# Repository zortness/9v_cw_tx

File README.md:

# 9V QRP Micro Transciever

Based on the schematic and work of Jeff Anderson, [K6JCA](https://www.qrz.com/db/k6jca)
and [this blog post](http://k6jca.blogspot.com/2009/08/9v-qrp-transceiver.html).

Thank you to Jeff for your help in debugging my implementation of your design.

## About

This is a very simple, direct conversion CW transciever that will operate on the 40m 
amateur radio band. It requires an external speaker or headphones, an external antenna,
and an external keyer for sending. 

This design is intended to allow modifying the center frequency of the transciever by
changing out the oscillator crystal without re-soldering any parts. 

**This is still a work in progress.**

I have devided up the functionality across two small PCBs and used a 8-pin jumper between them.
This gives a bit more room to spread out the components, and hopefully avoid unwanted interactions.
It should also give a bit larger ground plane, which should help with environmental sensitivity.

The transmitter has an observed harmonic transmission on 14m, which might necessitate an external 
band pass filter board at some point.

The power output in my experiements so far has been quite small, in the 50-100mW range. 

The effective receive and transmit frequencies can also be apart from one another by enough that
you may not hear someone responding directly on your transmit frequency. This seems to be worse
at either extreme of the VXO adjustment, but not verified by data yet.

## Schematics

## Board Layouts

## ProtoBoard Prototype 

This prototype is extremely sensitive to capacitance (even touch), and lacks a true ground plane,
though I added through-hole-pins to act as grounding feet on my steel work table. 

## SMD Prototypes

I've gone through a few SMD prototypes and made a number of pad and routing mistakes. I also chose
a number of parts poorly or just completely misread the units on the part values (nH != uH, pF != uF). 

I will update when one of the boards can operate without any further modification.

## SMD BOM
|Manufacturer Part Number|Manufacturer                     |Digi-Key Part Number      |Customer Reference              |Reference Designator            |Part Status|Quantity|Unit Price|Extended Price|
|------------------------|---------------------------------|--------------------------|--------------------------------|--------------------------------|-----------|--------|----------|--------------|
|MCP1703T-5002E/MB       |Microchip Technology             |MCP1703T-5002E/MBCT-ND    |[U1] 5V regulator               |U1                              |Active     |1       |0.54      |$0.54         |
|SA602AD/01,118          |NXP USA Inc.                     |568-1200-1-ND             |[U2] RF Mixer                   |U2                              |Active     |1       |2.88      |$2.88         |
|LM386MX-1/NOPB          |Texas Instruments                |LM386MX-1/NOPBCT-ND       |[U3] Audio Amp                  |U3                              |Active     |1       |1.02      |$1.02         |
|1N4148W-7-F             |Diodes Incorporated              |1N4148W-FDICT-ND          |[D1,2] diode                    |D1, D2                          |Active     |2       |0.16      |$0.32         |
|1SV281(TPH3,F)          |Toshiba Semiconductor and Storage|1SV281(TPH3F)CT-ND        |[D3] varicap diode              |D3                              |Active     |1       |0.36      |$0.36         |
|LBR2012T100K            |Taiyo Yuden                      |587-2045-1-ND             |[L1] inductor 10uH              |L1                              |Active     |1       |0.13      |$0.13         |
|CB2518T471K             |Taiyo Yuden                      |587-2194-1-ND             |[L2] inductor 470uH             |L2                              |Active     |1       |0.17      |$0.17         |
|MLF2012E5R6KT000        |TDK Corporation                  |445-1056-1-ND             |[L8] inductor 5.6uH             |L8                              |Active     |1       |0.18      |$0.18         |
|#B966AS-160M=P3         |Murata Electronics               |490-14125-1-ND            |[L4] inductor 16uH              |L4                              |Active     |1       |0.95      |$0.95         |
|MLF2012A1R2JT000        |TDK Corporation                  |445-181331-1-ND           |[L5] inductor 1.2uH             |L5                              |Active     |1       |0.22      |$0.22         |
|MLF1608C180KTA00        |TDK Corporation                  |445-1028-1-ND             |[L6] inductor 18uH              |L6                              |Active     |1       |0.17      |$0.17         |
|NL453232T-561J-PF       |TDK Corporation                  |445-NL453232T-561J-PFCT-ND|[L7] inductor 560uH             |L7                              |Active     |1       |0.43      |$0.43         |
|3362W-1-102LF           |Bourns Inc.                      |3362W-102LF-ND            |[R1] potentiometer 1k           |R1                              |Active     |1       |1.02      |$1.02         |
|3362W-1-253LF           |Bourns Inc.                      |3362W-253LF-ND            |[R2] potentiometer 25k          |R2                              |Active     |1       |1.02      |$1.02         |
|CRG0805F6K8             |TE Connectivity Passive Product  |A126384CT-ND              |[R3,5,6] resistor 6.8k          |R3, R5, R6                      |Active     |3       |0.1       |$0.30         |
|CRGCQ0805F1K5           |TE Connectivity Passive Product  |A129751CT-ND              |[R4] resistor 1.5k              |R4                              |Active     |1       |0.1       |$0.10         |
|2SCR574D3TL1            |Rohm Semiconductor               |2SCR574D3TL1CT-ND         |[Q2] NPN transistor 2A          |Q2                              |Active     |1       |0.82      |$0.82         |
|SJ-3502-SMT-TR          |CUI Devices                      |CP-3502SJCT-ND            |[J1] Audio Jack                 |J1                              |Active     |1       |1.22      |$1.22         |
|CON-SMA-EDGE-S          |RF Solutions                     |CON-SMA-EDGE-S-ND         |[J2] SMA-F edge connector       |J2                              |Active     |1       |1.69      |$1.69         |
|PH2-20-UA               |Adam Tech                        |2057-PH2-20-UA-ND         |[JP1] Jumper Pins Male          |JP1                             |Active     |1       |0.26      |$0.26         |
|PPPC042LFBN-RC          |Sullins Connector Solutions      |S7107-ND                  |[JP2] 8-pin Jumper Female       |JP2                             |Active     |1       |0.69      |$0.69         |
|PPPC031LGBN-RC          |Sullins Connector Solutions      |S5478-ND                  |[J3] 3-pin Female Crystal Socket|J3                              |Active     |1       |0.51      |$0.51         |
|968                     |Keystone Electronics             |36-968-ND                 |[B1] 9V battery connector       |B1                              |Active     |1       |1.48      |$1.48         |
|C0805C104Z5VACTU        |KEMET                            |399-1177-1-ND             |[C1,5,15] capacitor 0.1uF       |C1, C5, C15                     |Active     |3       |0.1       |$0.30         |
|C0805C330K5GACTU        |KEMET                            |399-8062-1-ND             |[C3,22,26] capacitor 33pF       |C3, C22, C26                    |Active     |3       |0.11      |$0.33         |
|CC0805JRNPO9BN271       |Yageo                            |311-1116-1-ND             |[C4] capacitor 270pF            |C4                              |Active     |1       |0.13      |$0.13         |
|CC0805KRX7R9BB391       |Yageo                            |311-1193-1-ND             |[C6,7] capacitor 390pF          |C6, C7                          |Active     |2       |0.12      |$0.24         |
|CC0805KRX7R9BB681       |Yageo                            |311-1126-1-ND             |[C8] capacitor 680pF            |C8                              |Active     |1       |0.11      |$0.11         |
|C0805C101JAGAC7800      |KEMET                            |399-15000-1-ND            |[C9] capacitor 100pF            |C9                              |Active     |1       |0.1       |$0.10         |
|C0805C151J5GACTU        |KEMET                            |399-1125-1-ND             |[C10,12,18] capacitor 150pF     |C10, C12, C18                   |Active     |3       |0.1       |$0.30         |
|C0805C470K5GACTU        |KEMET                            |399-8081-1-ND             |[C13] capacitor 47pF            |C13                             |Active     |1       |0.11      |$0.11         |
|C0805C221M5RACTU        |KEMET                            |399-8039-1-ND             |[C14] capacitor 220pF           |C14                             |Active     |1       |0.1       |$0.10         |
|RC0805FR-07100RL        |Yageo                            |311-100CRCT-ND            |[R7] resistor 100 Ohm           |R7                              |Active     |3       |0.1       |$0.30         |
|MMBT2222A-7-F           |Diodes Incorporated              |MMBT2222A-FDICT-ND        |[Q1] NPN Transistor .6A         |Q1                              |Active     |1       |0.13      |$0.13         |
|SJ-3523-SMT-TR          |CUI Devices                      |CP-3523SJCT-ND            |[J1] 3.5mm Stereo Phone Jack    |J1                              |Active     |1       |0.93      |$0.93         |
|GRM21BR61E106KA73K      |Murata Electronics               |490-16824-1-ND            |[C23,24,25] capacitor 10uF      |C23, C24, C25                   |Active     |3       |0.23      |$0.69         |
|C3216X5R1C336M160AB     |TDK Corporation                  |445-6002-1-ND             |[C22] capacitor 33pF            |C22                             |Active     |1       |1.03      |$1.03         |
|CL21B103KBANNNC         |Samsung Electro-Mechanics        |1276-1015-1-ND            |[C2,11,16,17,19,20,21] capacitor 10nF|C2, C11, C16, C17, C19, C20, C21|Active     |10      |0.045     |$0.45         |
|ASPI-0630LR-150M-T15    |Abracon LLC                      |ASPI-0630LR-150M-T15CT-ND |[L4] Inductor 15uH              |L4                              |Active     |1       |0.87      |$0.87         |
|SRP3012C-5R6M           |Bourns Inc.                      |118-SRP3012C-5R6MCT-ND    |[L3] Inductor 5.6uH             |                                |Active     |1       |0.96      |$0.96         |

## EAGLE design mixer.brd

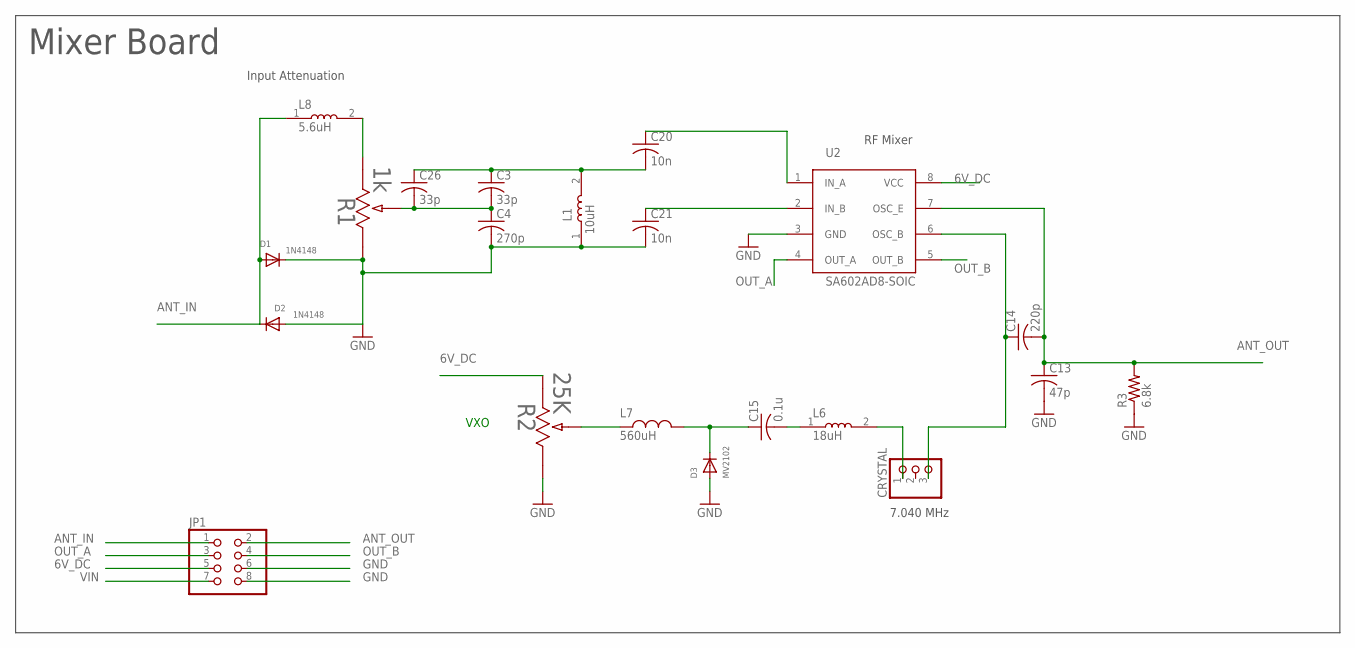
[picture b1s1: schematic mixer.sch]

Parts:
C3, C26: 33p; C0805
C4: 270p; C0805
C13: 47p; C0805
C14: 220p; C0805
C15: 0.1u; C0805
C20, C21: 10n; C0805
CRYSTAL: PINHD-1X3; 1X03
D1, D2: 1N4148; SOD-123FL
D3: MV2102; SOD-323F
JP1: PINHD-2X4; 2X04
L1: 10uH; INDC2012X87N
L6: 18uH; INDC2012X87N
L7: 560uH; INDM4532X32_W
L8: 5.6uH; INDC2012X87N
R1: 1k; POT_3362W
R2: 25K; POT_3362W
R3: 6.8k; M0805
U2: SA602AD8-SOIC; SOIC127P599X175-8N

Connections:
6V_DC: JP1.5, R2.1, U2.8 (VCC)
ANT_IN: D1.A, D2.C, JP1.1, L8.1
ANT_OUT: C13.1, C14.2, JP1.2, R3.2, U2.7 (OSC_E)
GND: C4.2, C13.2, C21.2, D1.C, D2.A, D3.A, JP1.6, JP1.8, L1.1, R1.3, R2.3, R3.1, U2.3 (GND)
unnamed: C20.1, U2.1 (IN_A)
unnamed: C21.1, U2.2 (IN_B)
unnamed: C3.1, C20.2, C26.1, L1.2
unnamed: C14.1, CRYSTAL.3, U2.6 (OSC_B)
unnamed: C3.2, C4.1, C26.2, R1.2
unnamed: L8.2, R1.1
unnamed: CRYSTAL.1, L6.2
unnamed: C15.2, L6.1
unnamed: C15.1, D3.C, L7.2
unnamed: L7.1, R2.2
OUT_A: JP1.3, U2.4 (OUT_A)
OUT_B: JP1.4, U2.5 (OUT_B)
VIN: JP1.7

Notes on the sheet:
Input Attenuation
RF Mixer
VXO
7.040 MHz
Mixer Board

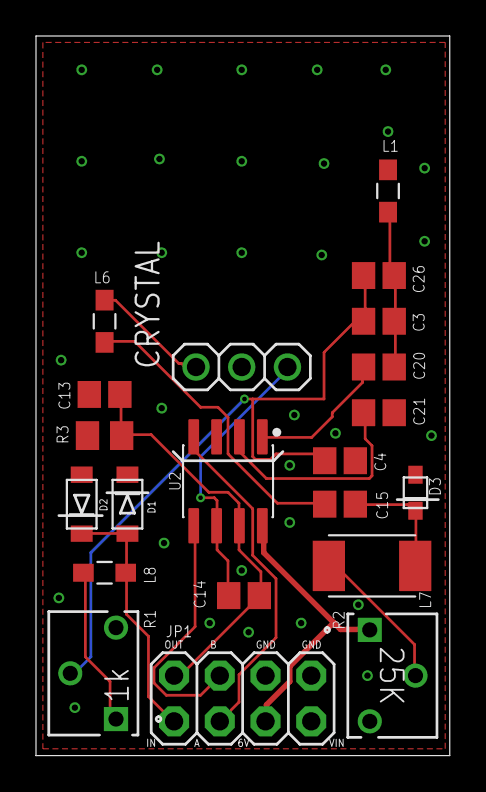
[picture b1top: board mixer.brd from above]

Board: 2 copper layers, 23.0 x 40.0 mm, 21 parts (0 on the bottom side), 16 nets.

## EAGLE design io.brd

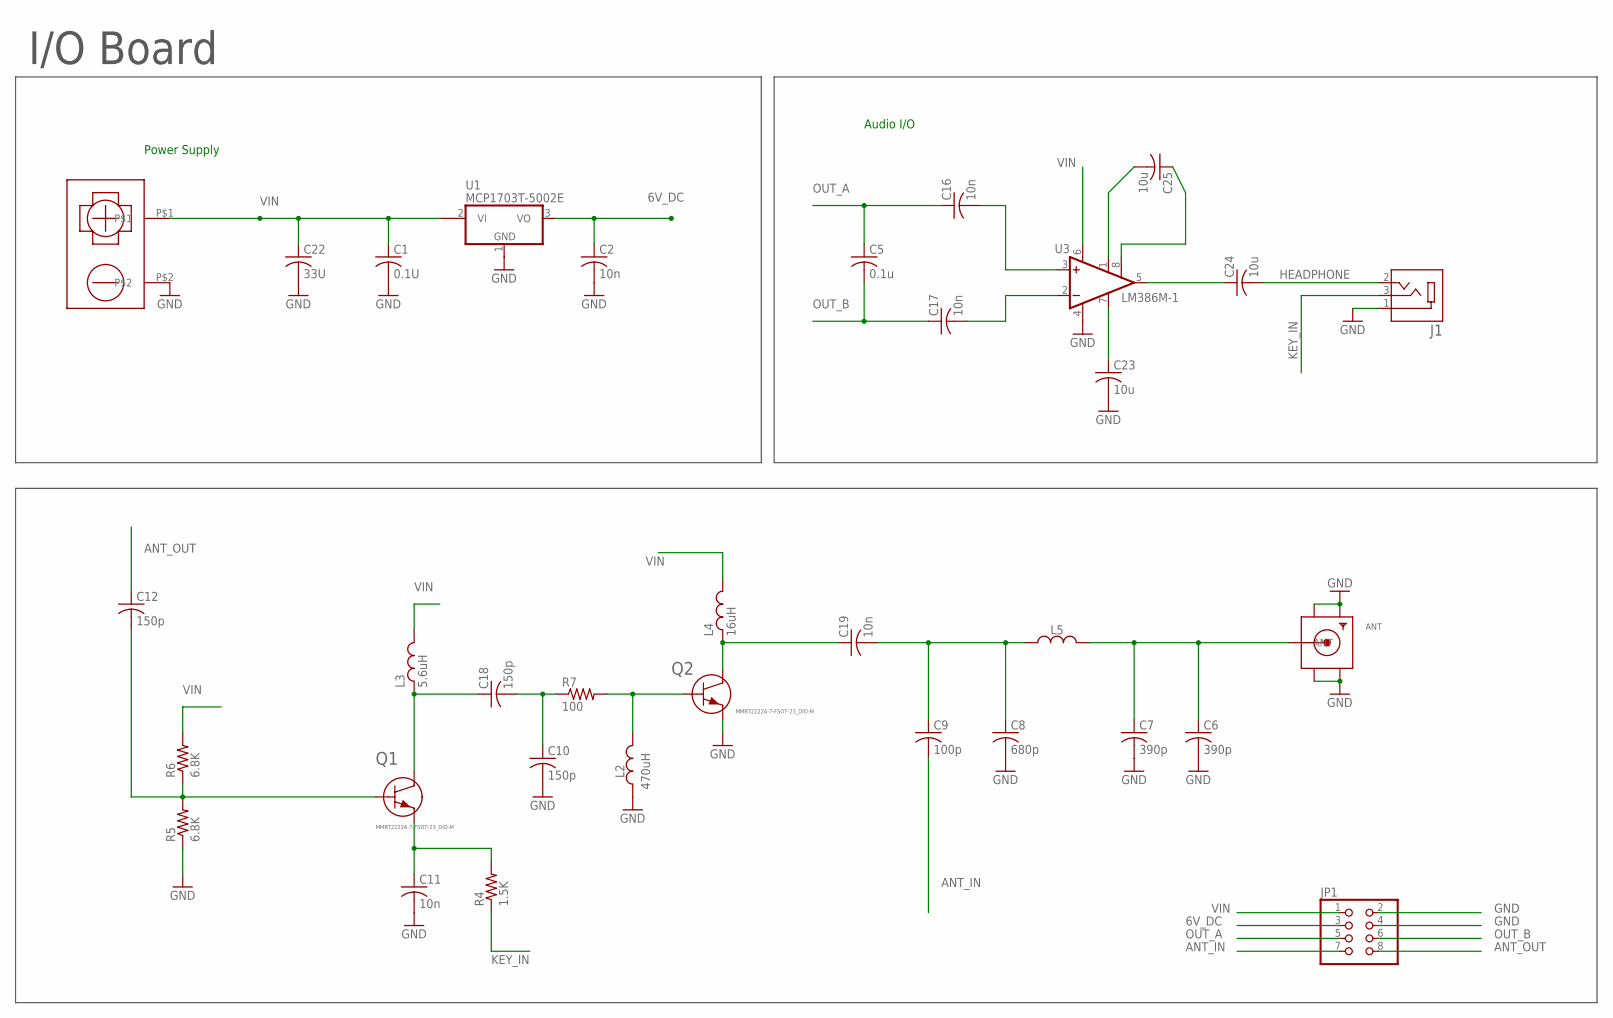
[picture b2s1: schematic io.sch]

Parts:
ANT: SMACONNECTOR_EDGE; SMA_EDGELAUNCH
C1: 0.1U; C0805
C2, C11, C16, C17: 10n; C0805
C5: 0.1u; C0805
C6, C7: 390p; C0805
C8: 680p; C0805
C9: 100p; C0805
C10, C12, C18: 150p; C0805
C19: 10n; C1206
C22: 33U; C1206
C23, C24, C25: 10u; C0805
J1: SJ-3523-SMT-TR; CUI_SJ-3523-SMT-TR
JP1: PINHD-2X4; 2X04
L2: 470uH; INDC2520X120N
L3: 5.6uH; SRP3012C
L4: 16uH; ASPI-0630LR
L5: 1.2uH; SRN4018TA
Q1, Q2: MMBT2222A-7-FSOT-23_DIO-M; SOT-23_DIO-M
R4: 1.5K; M0805
R5, R6: 6.8K; M0805
R7: 100; M0805
U1: MCP1703T-5002E; SOT89
U3: LM386M-1; SO08
U$1: 9V_9689V_968_SMD; 9V_968_PAD

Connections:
6V_DC: C2.1, JP1.3, U1.3 (VO)
ANT_IN: C9.2, JP1.7
ANT_OUT: C12.1, JP1.8
GND: ANT.GND@1 (GND4), ANT.GND@3 (GND2), C1.2, C2.2, C6.2, C7.2, C8.2, C10.2, C11.2, C22.2, C23.2, J1.1, JP1.2, JP1.4, L2.1, R5.1, U1.1 (GND), U3.4 (GND), U$1.P$2
HEADPHONE: C24.2, J1.2
KEY_IN: J1.3, R4.1
unnamed: C16.2, U3.3 (+IN)
unnamed: C17.2, U3.2 (-IN)
unnamed: C23.1, U3.7 (BYPASS)
unnamed: C25.1, U3.8 (GAIN)
unnamed: C25.2, U3.1 (GAIN)
unnamed: C24.1, U3.5 (OUT)
unnamed: C12.2, Q1.1, R5.2, R6.1
unnamed: C11.1, Q1.2 (3), R4.2
unnamed: C18.1, L3.P$1 (1), Q1.3 (2)
unnamed: C10.1, C18.2, R7.1
unnamed: L2.2, Q2.1, R7.2
unnamed: C19.1, L4.P$1 (1), Q2.3 (2)
unnamed: C8.1, C9.1, C19.2, L5.P$1 (1)
unnamed: ANT.P (ANT), C6.1, C7.1, L5.P$2 (2)
OUT_A: C5.1, C16.1, JP1.5
OUT_B: C5.2, C17.1, JP1.6
VIN: C1.1, C22.1, JP1.1, L3.P$2 (2), L4.P$2 (2), R6.2, U1.2@1 (VI1), U3.6 (VS), U$1.P$1

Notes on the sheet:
Power Supply
Audio I/O
I/O Board

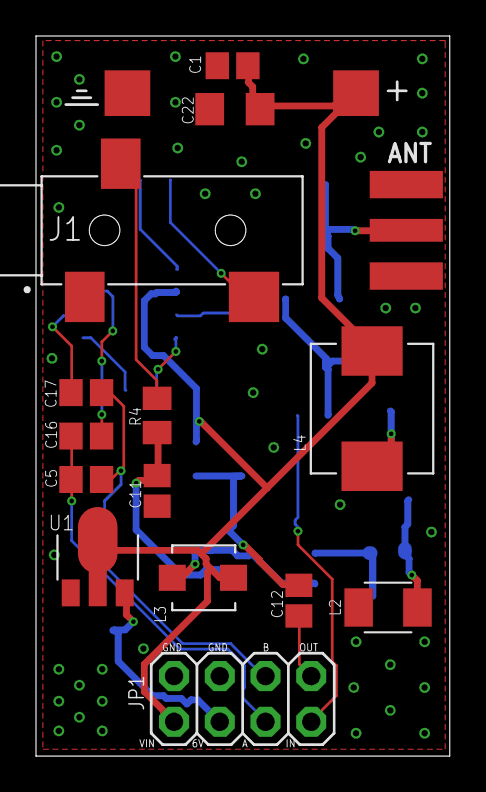
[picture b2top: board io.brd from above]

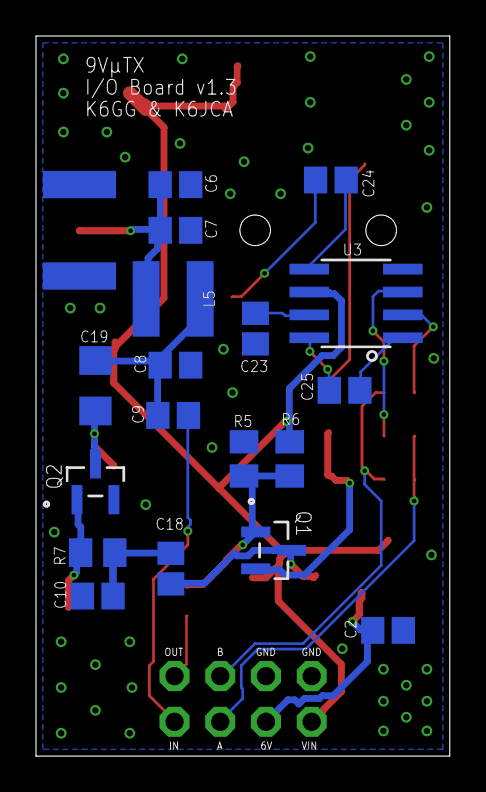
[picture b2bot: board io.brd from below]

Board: 2 copper layers, 23.0 x 40.0 mm, 34 parts (18 on the bottom side), 23 nets.

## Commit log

2020-05-26 initial commit
    An initial copy of K6JCA's CW transciever packaged in a 9V battery
2020-05-27 first attempt at board layout
2020-05-31 splitting boards, doing layouts
    Split into two boards with jumpers between. Added jumper for crystal to be able to change reference frequency. Closer to real layouts, still need to solidify some parts.
2020-06-02 updating layouts and parts
2020-07-18 updated Q1, added readme
    Updated Q1 to be a better replacement for the original PN2222A in an SMD format. Also added a readme, with links to PNGs of the schematics and layout renderings, as well as a photo of one of my proto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
2020-07-18 about section for readme
2020-07-18 forgot to save mixer schematic
    Forgot to save while adjusting the schematic layout to make it more readable
2020-07-25 cleaned up boards, new screenshots
    Cleaned up the orientation and text on the boards. Ran them through the OshPark rules, and sent off v1 to get printed
2020-08-14 Updated boarts to v1.1
    9VuTX Version 1.1
    Several adjustments after mockup with V 1.0 of the board. That first version would be non-functional due to a few layout mismatches.
    * fixed 2nd transistor layout to actually match part / spec (TO-252)
    * rotated potentiometers 180 degrees so they face outward instead toward the middle of the board
    * expanded pads of L2 (450uH inductor) to match recommended spec
    * replaced phone jack with a true surface mount version (SJ-3523-SMT-TR)
2020-08-14 continuing on v 1.1
    * removed "label" label from SMA connector
    * increased the width of some lines likely to carry higher current
    * attempted to clean up some little stuff
    * updated images
2020-08-18 Mixer board to 1.1a
    Realized the jumper on the Mixer board was not oriented correctly. Unfortunately already ordered some of the previous version, so this is a new version.
2020-08-18 Moving Mixer JP1 label
2020-09-01 Mixer board 1.1b
    * fixed pad size for L7
2020-10-11 v1.1a of I/O board
    * Q2 pinout was wrong, pins 2 and 3 were swapped
2020-10-16 Working on 1.1a of I/O after testing
    * replaced L4 with a much smaller component
2020-10-17 Continuing on V1.1a of the I/O board
    * re-placed Q1 on the layout
    * updated images
2020-10-17 Some cleanup
    * mixer board had incorrect Resistor labels
    * updated schematic PNG
2020-11-21 v1.2 boards
    * corrected C22 as a 33uF (vs 33pF) capacitor with a 1206 footprint
    * Q2 emitter is now tied to Q1 emitter and KEY_IN to cut down on self resonance
    * Unused pin 4 on JP1 now tied to GND
    * All pins on JP1 labelled on top and bottom of each board
    * lots more GND vias
2020-11-23 v1.2 updated inductors
    * updated L3 to a 650mA capable 5.6uH flat package
    * updated L4 to a 3A capable 15uH flat package... 16uH are difficult to come by
    * general board cleanup for readability
2020-11-23 Image updates
    * new boards and schematics
    * new photos of smd prototypes
2020-11-23 Update README to contain BOM
    Added a Bill of Materials (BOM) for the SMD prototype v1.2
2020-11-24 Version 1.2 as ordered
    * some slight cleanup in labels and routing after looking at the previews on oshpark
2020-12-20 v1.3
    * replaced L5 and C19 with larger devices capable of more current
    * replaced Q2 with another 2222A
    * increased power and output wire size to 15mil (from 12)
    Revisions based on testing with my amplifier circuit breakout
